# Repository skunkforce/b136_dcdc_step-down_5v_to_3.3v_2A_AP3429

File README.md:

# edgy_board number b136
This design is part of the [edgy board project](https://github.com/skunkforce/edgy_boards). It provides a 2A step-down from 5v to 3.3v using AP3429. 

# getting started
This repository uses submodules. After cloning use the command 

```$ git submodule update --init --recursive```

to pull the submodules before opening the project with kicad. 

# Tests
Tests can be found in [TESTS.md](TESTS.md)

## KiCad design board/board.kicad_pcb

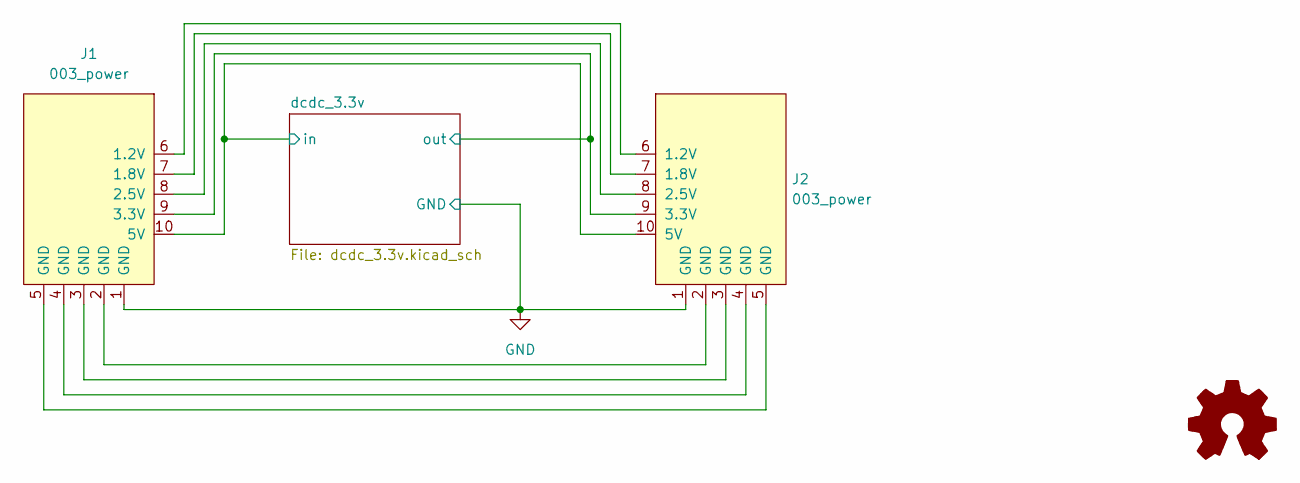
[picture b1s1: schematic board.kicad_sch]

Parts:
J1: 003_power; on_edge_2x05_device
J2: 003_power; on_edge_2x05_host
LOGO1: Logo_Open_Hardware_Small; OSHW-Symbol_6.7x6mm_SilkScreen

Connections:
/dcdc_3.3v/in: J1.10 (5V), J2.10 (5V); also elsewhere on the board
/dcdc_3.3v/out: J1.9 (3.3V), J2.9 (3.3V); also elsewhere on the board
GND: J1.1 (GND), J2.1 (GND); also elsewhere on the board
unnamed: J1.2 (GND), J2.2 (GND)
unnamed: J1.3 (GND), J2.3 (GND)
unnamed: J1.4 (GND), J2.4 (GND)
unnamed: J1.5 (GND), J2.5 (GND)
unnamed: J1.6 (1.2V), J2.6 (1.2V)
unnamed: J1.7 (1.8V), J2.7 (1.8V)
unnamed: J1.8 (2.5V), J2.8 (2.5V)

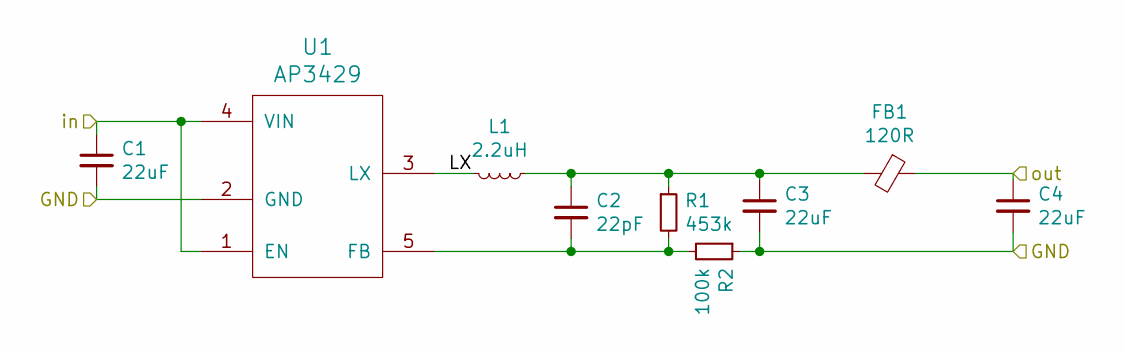
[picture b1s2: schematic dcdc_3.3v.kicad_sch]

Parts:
C1, C3, C4: 22uF; C_0603_1608Metric
C2: 22pF; C_0402_1005Metric
FB1: 120R; R_0805_2012Metric
L1: 2.2uH; L_Taiyo-Yuden_NR-50xx; MPN NRS5030T2R2NMGJ
R1: 453k; C_0402_1005Metric
R2: 100k; C_0402_1005Metric
U1: AP3429; TSOT-23-5; MPN AP3429AKTTR-G1

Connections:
/dcdc_3.3v/LX: L1.2, U1.3 (LX)
/dcdc_3.3v/in: C1.1, U1.1 (EN), U1.4 (VIN); also elsewhere on the board
/dcdc_3.3v/out: C4.1, FB1.1; also elsewhere on the board
GND: C1.2, C3.2, C4.2, R2.1, U1.2 (GND); also elsewhere on the board
unnamed: C2.1, C3.1, FB1.2, L1.1, R1.1
unnamed: C2.2, R1.2, R2.2, U1.5 (FB)

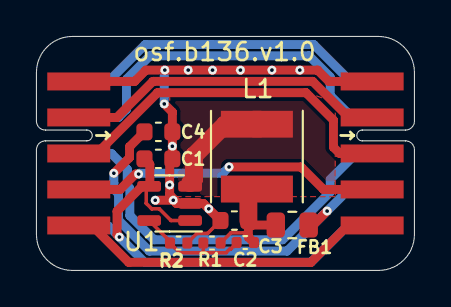
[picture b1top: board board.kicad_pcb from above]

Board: 2 copper layers, 21.0 x 13.0 mm, 12 parts (1 on the bottom side), 13 nets.

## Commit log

2023-05-30 initial
